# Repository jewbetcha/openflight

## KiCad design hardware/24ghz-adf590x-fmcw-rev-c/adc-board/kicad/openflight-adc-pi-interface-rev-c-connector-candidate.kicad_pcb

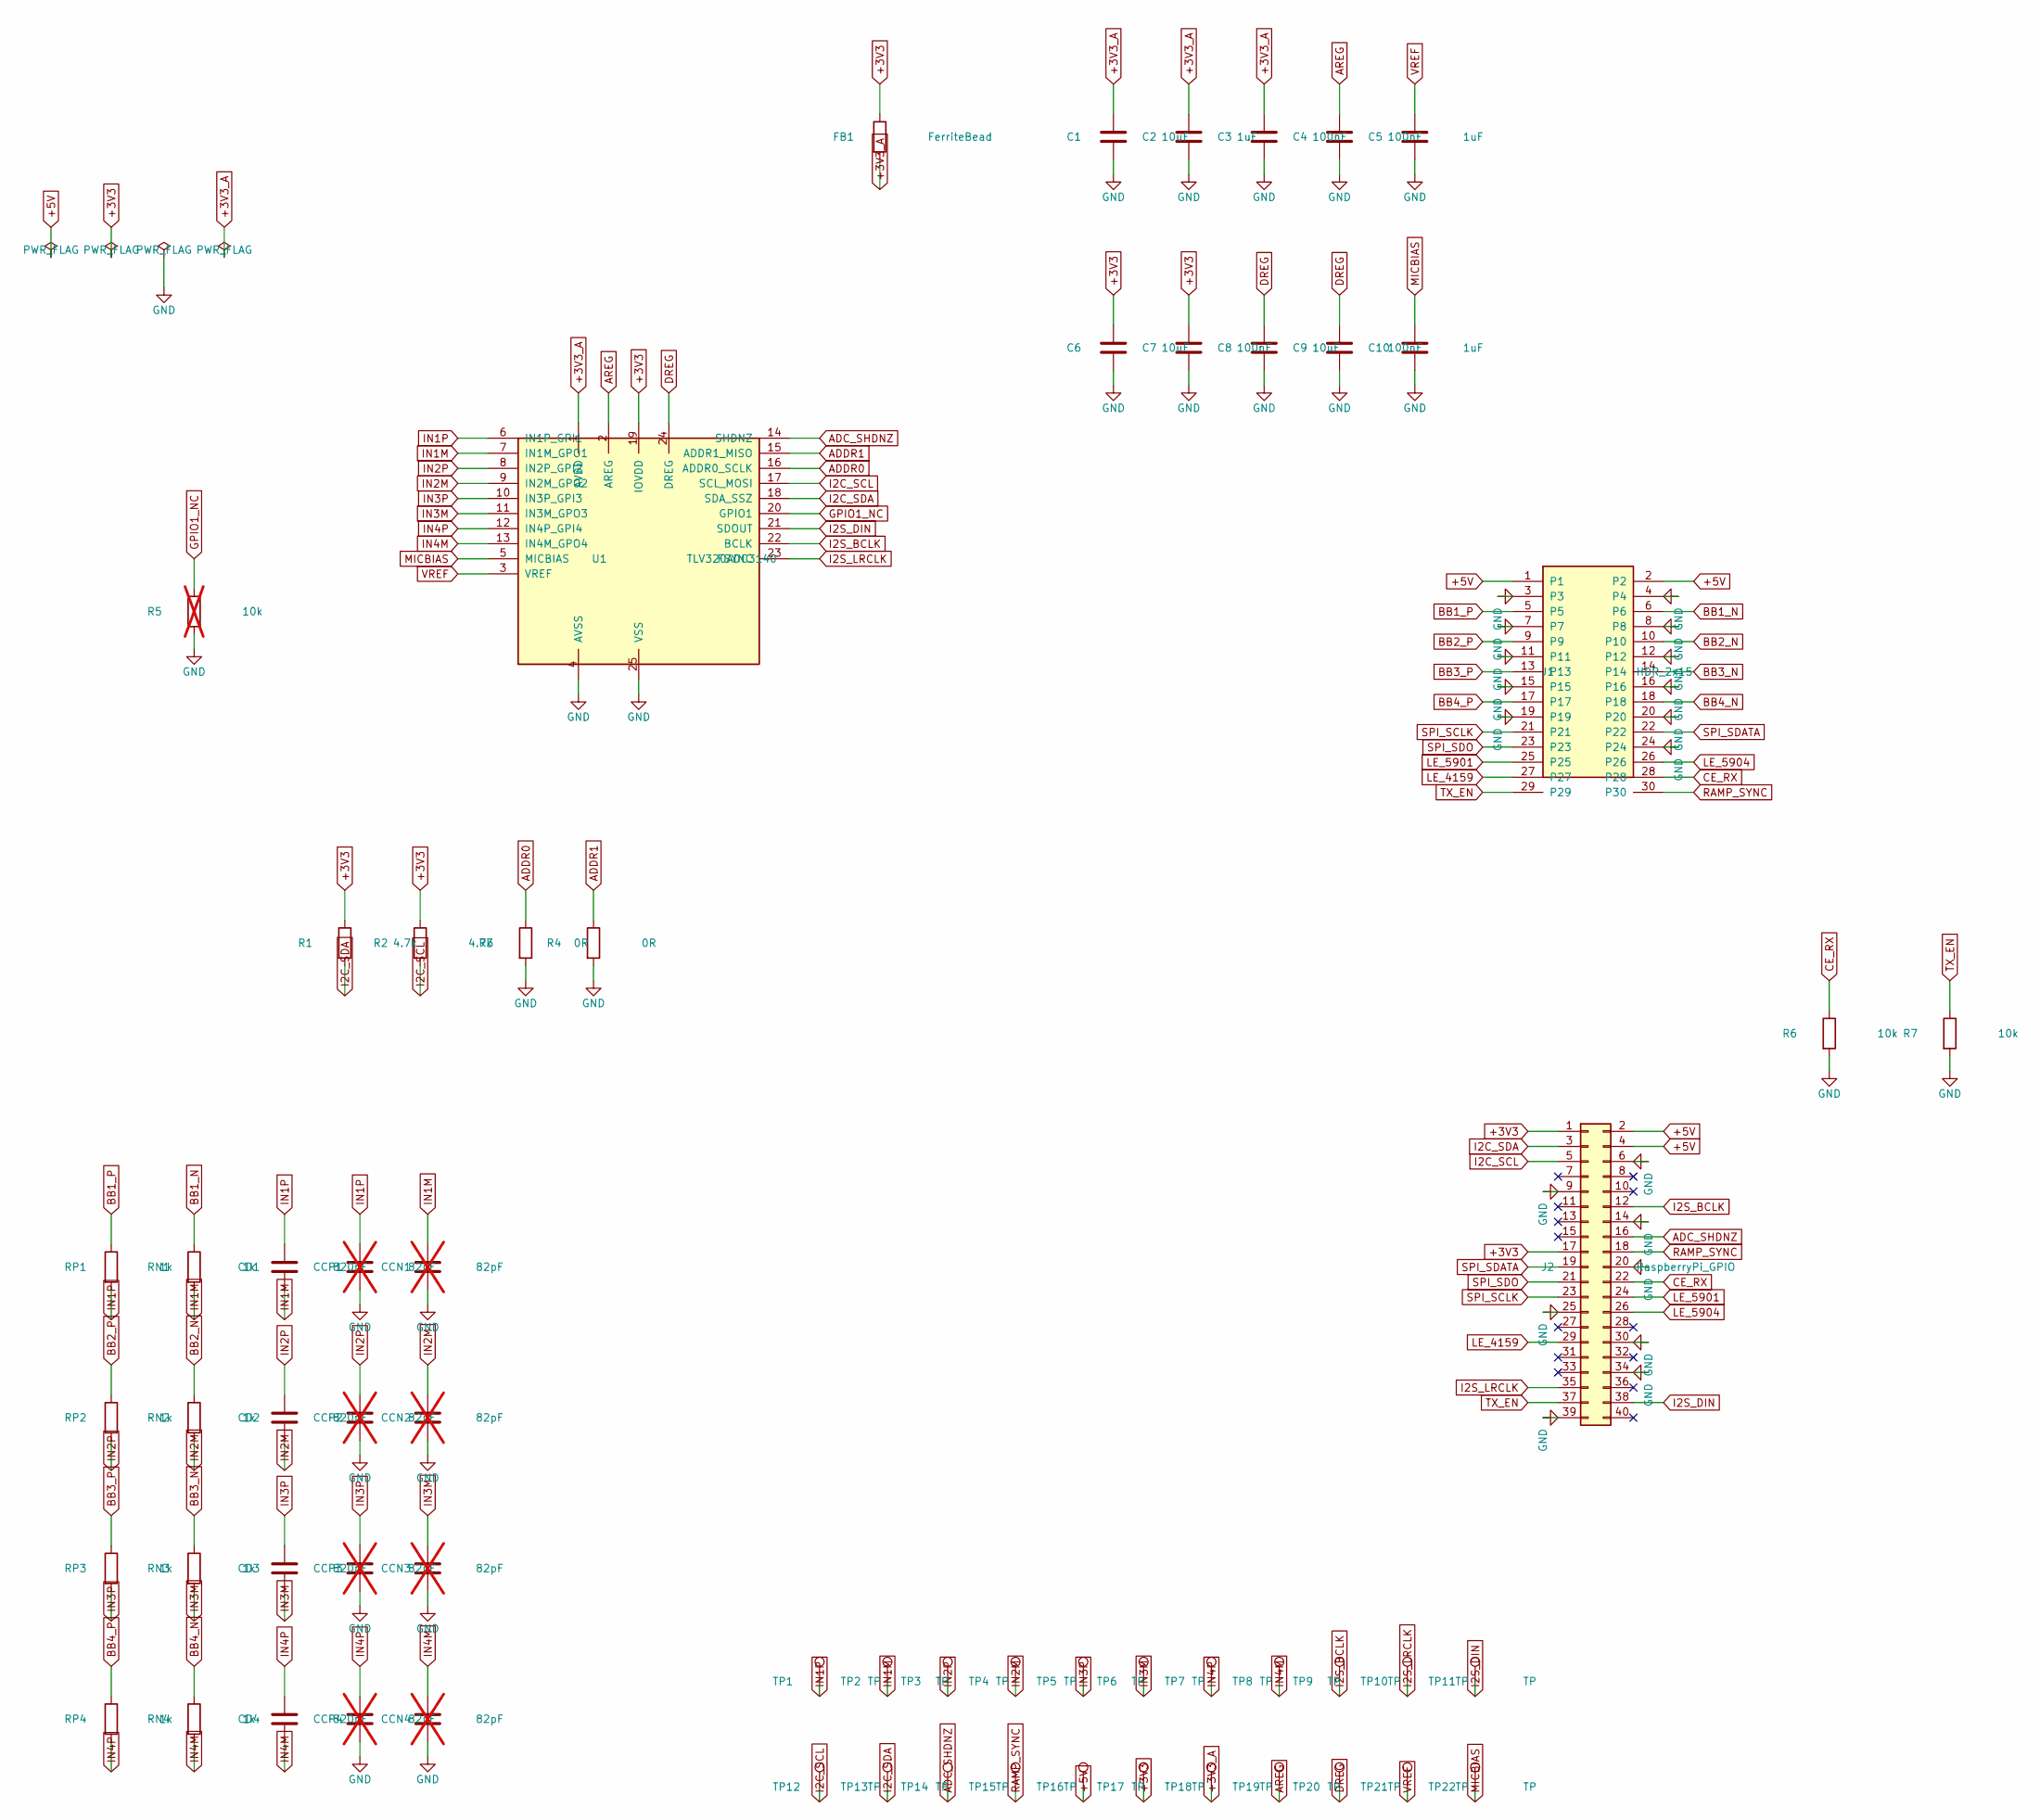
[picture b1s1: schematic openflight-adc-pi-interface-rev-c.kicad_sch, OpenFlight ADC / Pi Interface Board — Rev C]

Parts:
C1, C6, C8: 10uF; C_0402_1005Metric
C2, C5, C10: 1uF; C_0402_1005Metric
C3, C4, C7, C9: 100nF; C_0402_1005Metric
CCN1, CCN2, CCN3, CCN4: 82pF; C_0402_1005Metric; not fitted
CCP1, CCP2, CCP3, CCP4: 82pF; C_0402_1005Metric; not fitted
CD1, CD2, CD3, CD4: 820pF; C_0402_1005Metric
FB1: FerriteBead; R_0402_1005Metric
J1: HDR_2x15; HDR_2x15_1.27MM_SMD; MPN FTSH-115-01-L-DV-K
J2: RaspberryPi_GPIO; PinSocket_2x20_P2.54mm_Vertical; MPN ESQ-120-58-S-D
R1, R2: 4.7k; R_0402_1005Metric
R3, R4: 0R; R_0402_1005Metric
R5: 10k; R_0402_1005Metric; not fitted
R6, R7: 10k; R_0402_1005Metric; MPN RC0402FR-0710KL
RN1, RN2, RN3, RN4: 1k; R_0402_1005Metric
RP1, RP2, RP3, RP4: 1k; R_0402_1005Metric
TP1, TP2, TP3, TP4, TP5, TP6, TP7, TP8, TP9, TP10, TP11, TP12, TP13, TP14, TP15, TP16, TP17, TP18, TP19, TP20, TP21, TP22: TP; TestPoint_Pad_D1.5mm
U1: TLV320ADC3140; TLV320ADC3140_WQFN24; MPN TLV320ADC3140IRTWT

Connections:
+3V3: C6.1, C7.1, FB1.1, J2.1, J2.17, R1.1, R2.1, TP17.1, U1.19 (IOVDD)
+3V3_A: C1.1, C2.1, C3.1, FB1.2, TP18.1, U1.1 (AVDD)
+5V: J1.1, J1.2, J2.2, J2.4, TP16.1
ADC_SHDNZ: J2.16, TP14.1, U1.14 (SHDNZ)
ADDR0: R3.1, U1.16 (ADDR0_SCLK)
ADDR1: R4.1, U1.15 (ADDR1_MISO)
AREG: C4.1, TP19.1, U1.2 (AREG)
BB1_N: J1.6, RN1.1
BB1_P: J1.5, RP1.1
BB2_N: J1.10, RN2.1
BB2_P: J1.9, RP2.1
BB3_N: J1.14, RN3.1
BB3_P: J1.13, RP3.1
BB4_N: J1.18, RN4.1
BB4_P: J1.17, RP4.1
CE_RX: J1.28, J2.22, R6.1
DREG: C8.1, C9.1, TP20.1, U1.24 (DREG)
GND: C1.2, C2.2, C3.2, C4.2, C5.2, C6.2, C7.2, C8.2, C9.2, C10.2, CCN1.2, CCN2.2, CCN3.2, CCN4.2, CCP1.2, CCP2.2, CCP3.2, CCP4.2, J1.3, J1.4, J1.7, J1.8, J1.11, J1.12, J1.15, J1.16, J1.19, J1.20, J1.24, J2.6, J2.9, J2.14, J2.20, J2.25, J2.30, J2.34, J2.39, R3.2, R4.2, R5.2, R6.2, R7.2, U1.4 (AVSS), U1.25 (VSS)
GPIO1_NC: R5.1, U1.20 (GPIO1)
I2C_SCL: J2.5, R2.2, TP12.1, U1.17 (SCL_MOSI)
I2C_SDA: J2.3, R1.2, TP13.1, U1.18 (SDA_SSZ)
I2S_BCLK: J2.12, TP9.1, U1.22 (BCLK)
I2S_DIN: J2.38, TP11.1, U1.21 (SDOUT)
I2S_LRCLK: J2.35, TP10.1, U1.23 (FSYNC)
IN1M: CCN1.1, CD1.2, RN1.2, TP2.1, U1.7 (IN1M_GPO1)
IN1P: CCP1.1, CD1.1, RP1.2, TP1.1, U1.6 (IN1P_GPI1)
IN2M: CCN2.1, CD2.2, RN2.2, TP4.1, U1.9 (IN2M_GPO2)
IN2P: CCP2.1, CD2.1, RP2.2, TP3.1, U1.8 (IN2P_GPI2)
IN3M: CCN3.1, CD3.2, RN3.2, TP6.1, U1.11 (IN3M_GPO3)
IN3P: CCP3.1, CD3.1, RP3.2, TP5.1, U1.10 (IN3P_GPI3)
IN4M: CCN4.1, CD4.2, RN4.2, TP8.1, U1.13 (IN4M_GPO4)
IN4P: CCP4.1, CD4.1, RP4.2, TP7.1, U1.12 (IN4P_GPI4)
LE_4159: J1.27, J2.29
LE_5901: J1.25, J2.24
LE_5904: J1.26, J2.26
MICBIAS: C10.1, TP22.1, U1.5 (MICBIAS)
RAMP_SYNC: J1.30, J2.18, TP15.1
SPI_SCLK: J1.21, J2.23
SPI_SDATA: J1.22, J2.19
SPI_SDO: J1.23, J2.21
TX_EN: J1.29, J2.37, R7.1
VREF: C5.1, TP21.1, U1.3 (VREF)

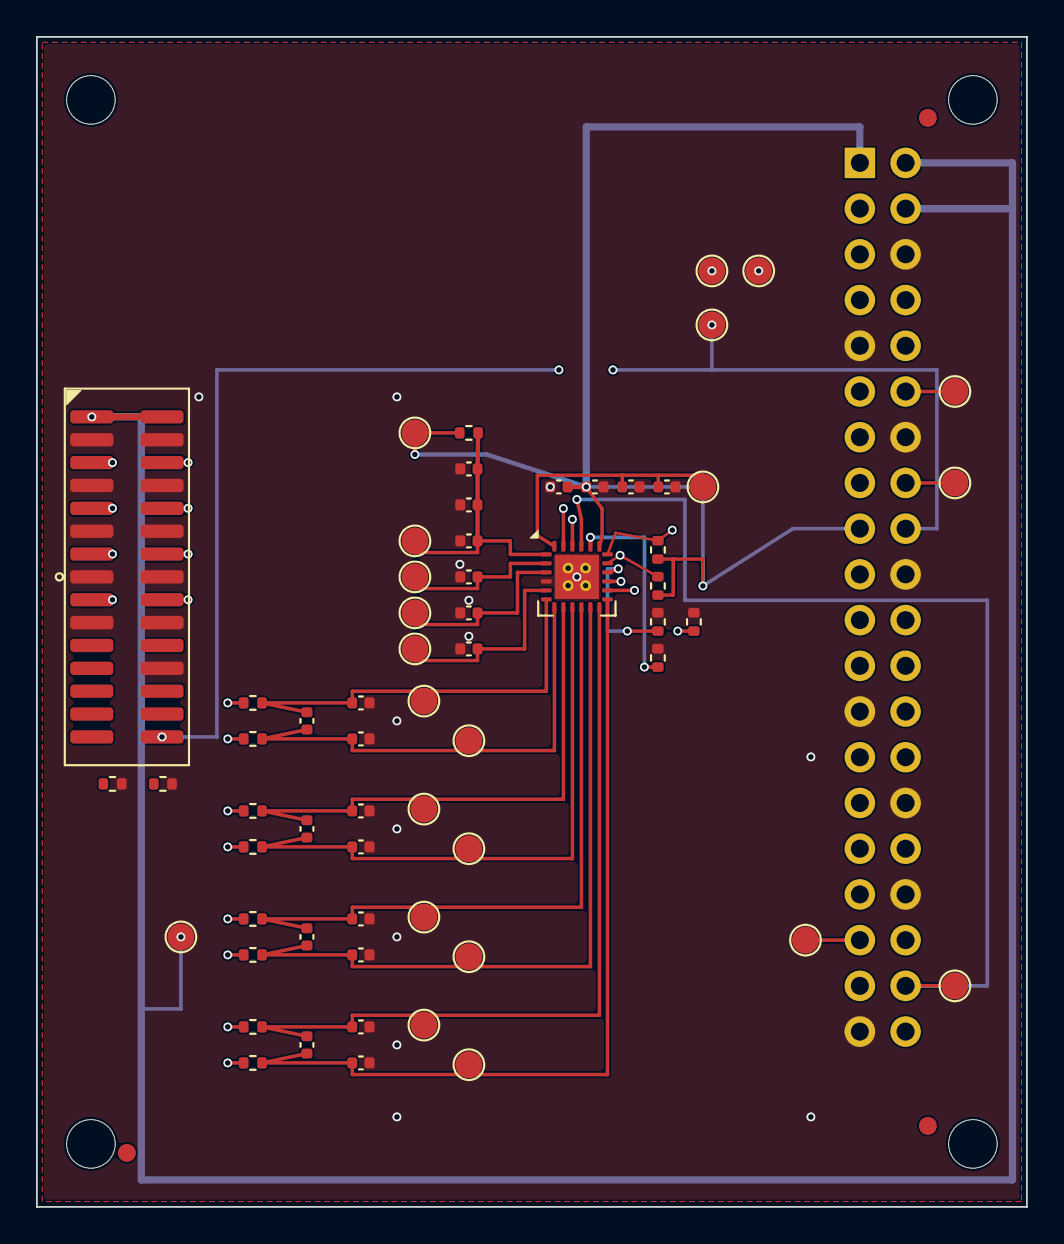
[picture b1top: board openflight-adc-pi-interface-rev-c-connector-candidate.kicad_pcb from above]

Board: 4 copper layers, 55.0 x 65.0 mm, 70 parts (1 on the bottom side), 42 nets.

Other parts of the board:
FID1, FID2, FID3: Fiducial_1mm
H1, H2, H3, H4: MountingHole_2.7mm

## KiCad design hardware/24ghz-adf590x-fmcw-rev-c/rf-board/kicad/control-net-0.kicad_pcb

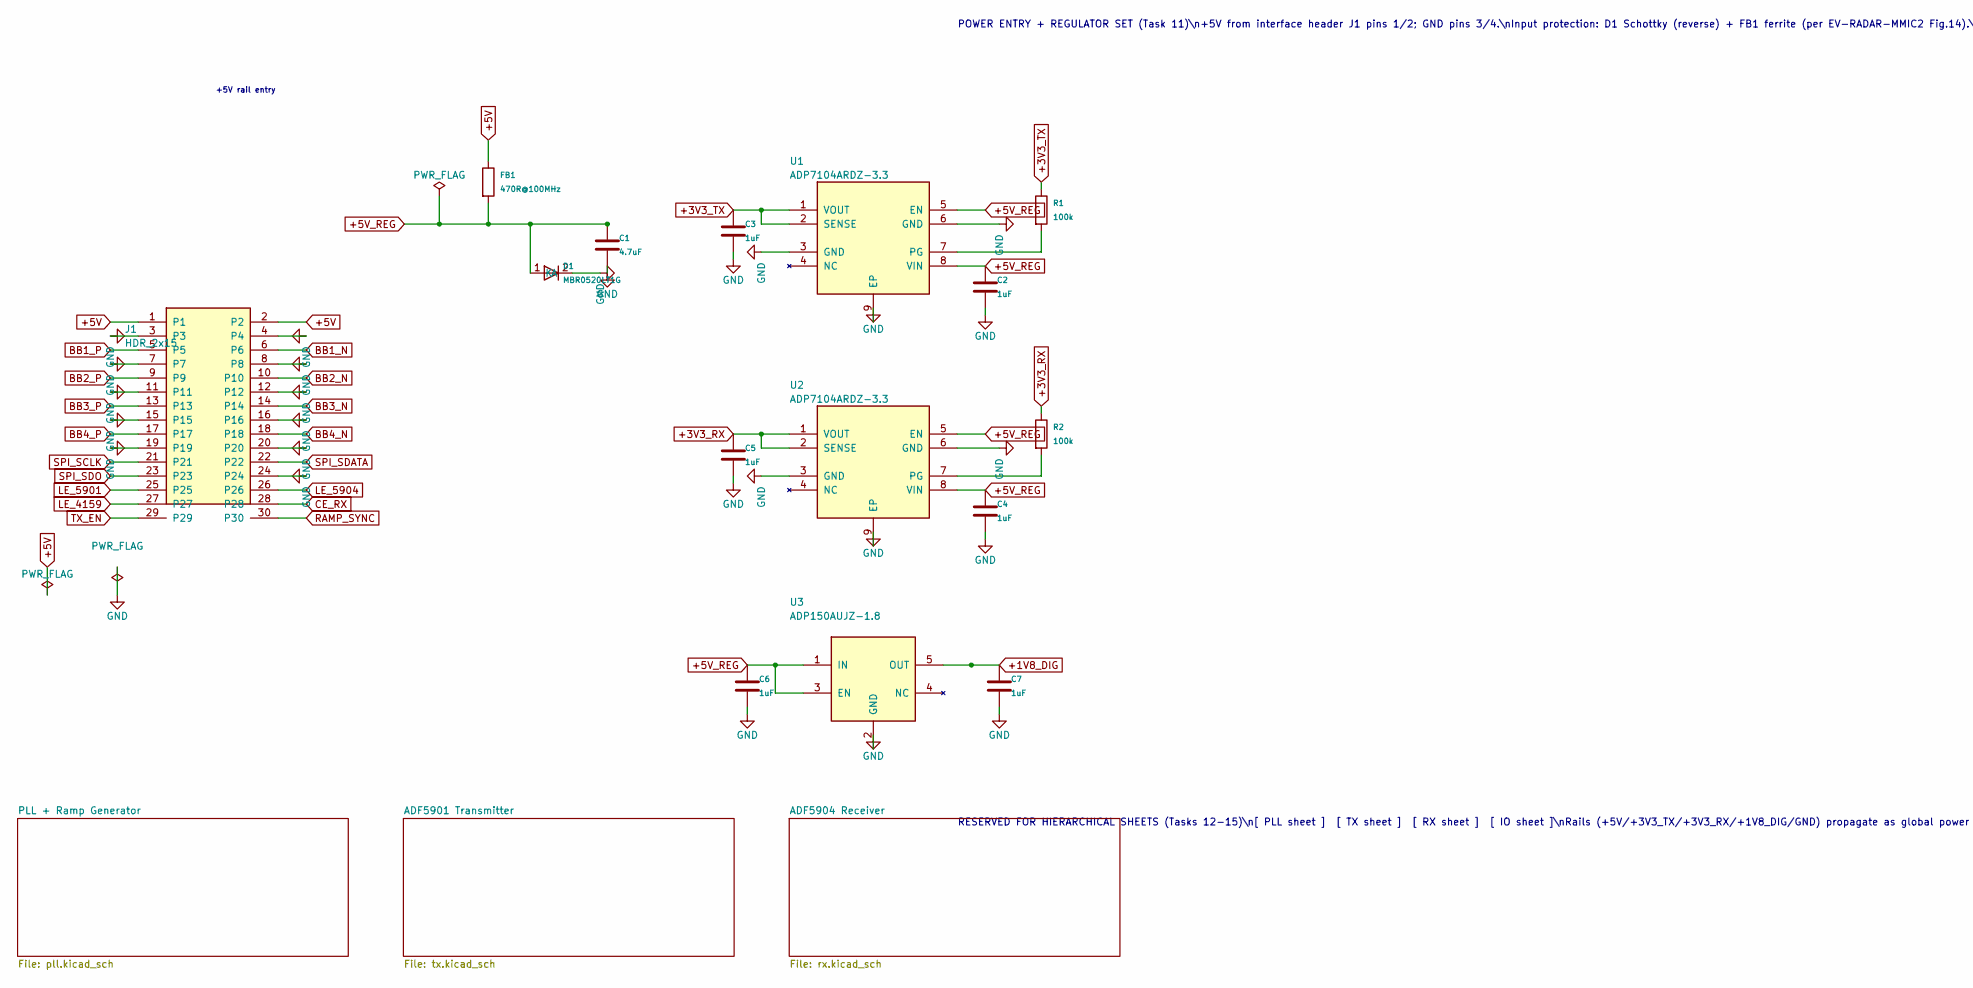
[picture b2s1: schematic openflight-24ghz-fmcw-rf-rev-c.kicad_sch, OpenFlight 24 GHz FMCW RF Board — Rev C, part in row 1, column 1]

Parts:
C1: 4.7uF; C_0603_1608Metric
C2, C3, C4, C5, C6, C7: 1uF; C_0603_1608Metric
D1: MBR0520LT1G; D_SOD-123; MPN MBR0520LT1G
FB1: 470R@100MHz; L_0603_1608Metric; MPN 742792642
J1: HDR_2x15; HDR_2x15_1.27MM_SMD; MPN FTSH-115-01-L-DV-K
R1, R2: 100k; R_0402_1005Metric
U1, U2: ADP7104ARDZ-3.3; ADP7104_SOIC8_EP; MPN ADP7104ARDZ-3.3
U3: ADP150AUJZ-1.8; ADP150_TSOT23_5; MPN ADP150AUJZ-1.8

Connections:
+1V8_DIG: C7.1, U3.5 (OUT); also elsewhere on the board
+3V3_RX: C5.1, R2.1, U2.1 (VOUT), U2.2 (SENSE); also elsewhere on the board
+3V3_TX: C3.1, R1.1, U1.1 (VOUT), U1.2 (SENSE); also elsewhere on the board
+5V: FB1.1, J1.1, J1.2; also elsewhere on the board
+5V_REG: C1.1, C2.1, C4.1, C6.1, D1.1 (K), FB1.2, U1.5 (EN), U1.8 (VIN), U2.5 (EN), U2.8 (VIN), U3.1 (IN), U3.3 (EN)
CE_RX: J1.28; also elsewhere on the board
LE_4159: J1.27; also elsewhere on the board
LE_5901: J1.25; also elsewhere on the board
LE_5904: J1.26; also elsewhere on the board
unnamed: R1.2, U1.7 (PG)
unnamed: R2.2, U2.7 (PG)
RAMP_SYNC: J1.30; also elsewhere on the board
SPI_SCLK: J1.21; also elsewhere on the board
SPI_SDATA: J1.22; also elsewhere on the board
SPI_SDO: J1.23; also elsewhere on the board
TX_EN: J1.29; also elsewhere on the board

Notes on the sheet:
POWER ENTRY + REGULATOR SET (Task 11)\n+5V from interface header J1 pins 1/2; GND pins 3/4.\nInput protection: D1 Schottky (reverse) + FB1 ferrite (per EV-RADAR-MMIC2 Fig.14).\nU1 ADP7104-3.3 -> +3V3_TX (ADF5901). U2 ADP7104-3.3 -> +3V3_RX (ADF5904 + ADF4159 analog).\nU3 ADP150-1.8 -> +1V8_DIG (ADF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
RESERVED FOR HIERARCHICAL SHEETS (Tasks 12-15)\n[ PLL sheet ] [ TX sheet ] [ RX sheet ] [ IO sheet ]\nRails (+5V/+3V3_TX/+3V3_RX/+1V8_DIG/GND) propagate as global power symbols;\nsignals cross via hierarchical pins added by those tasks.
+5V rail entry

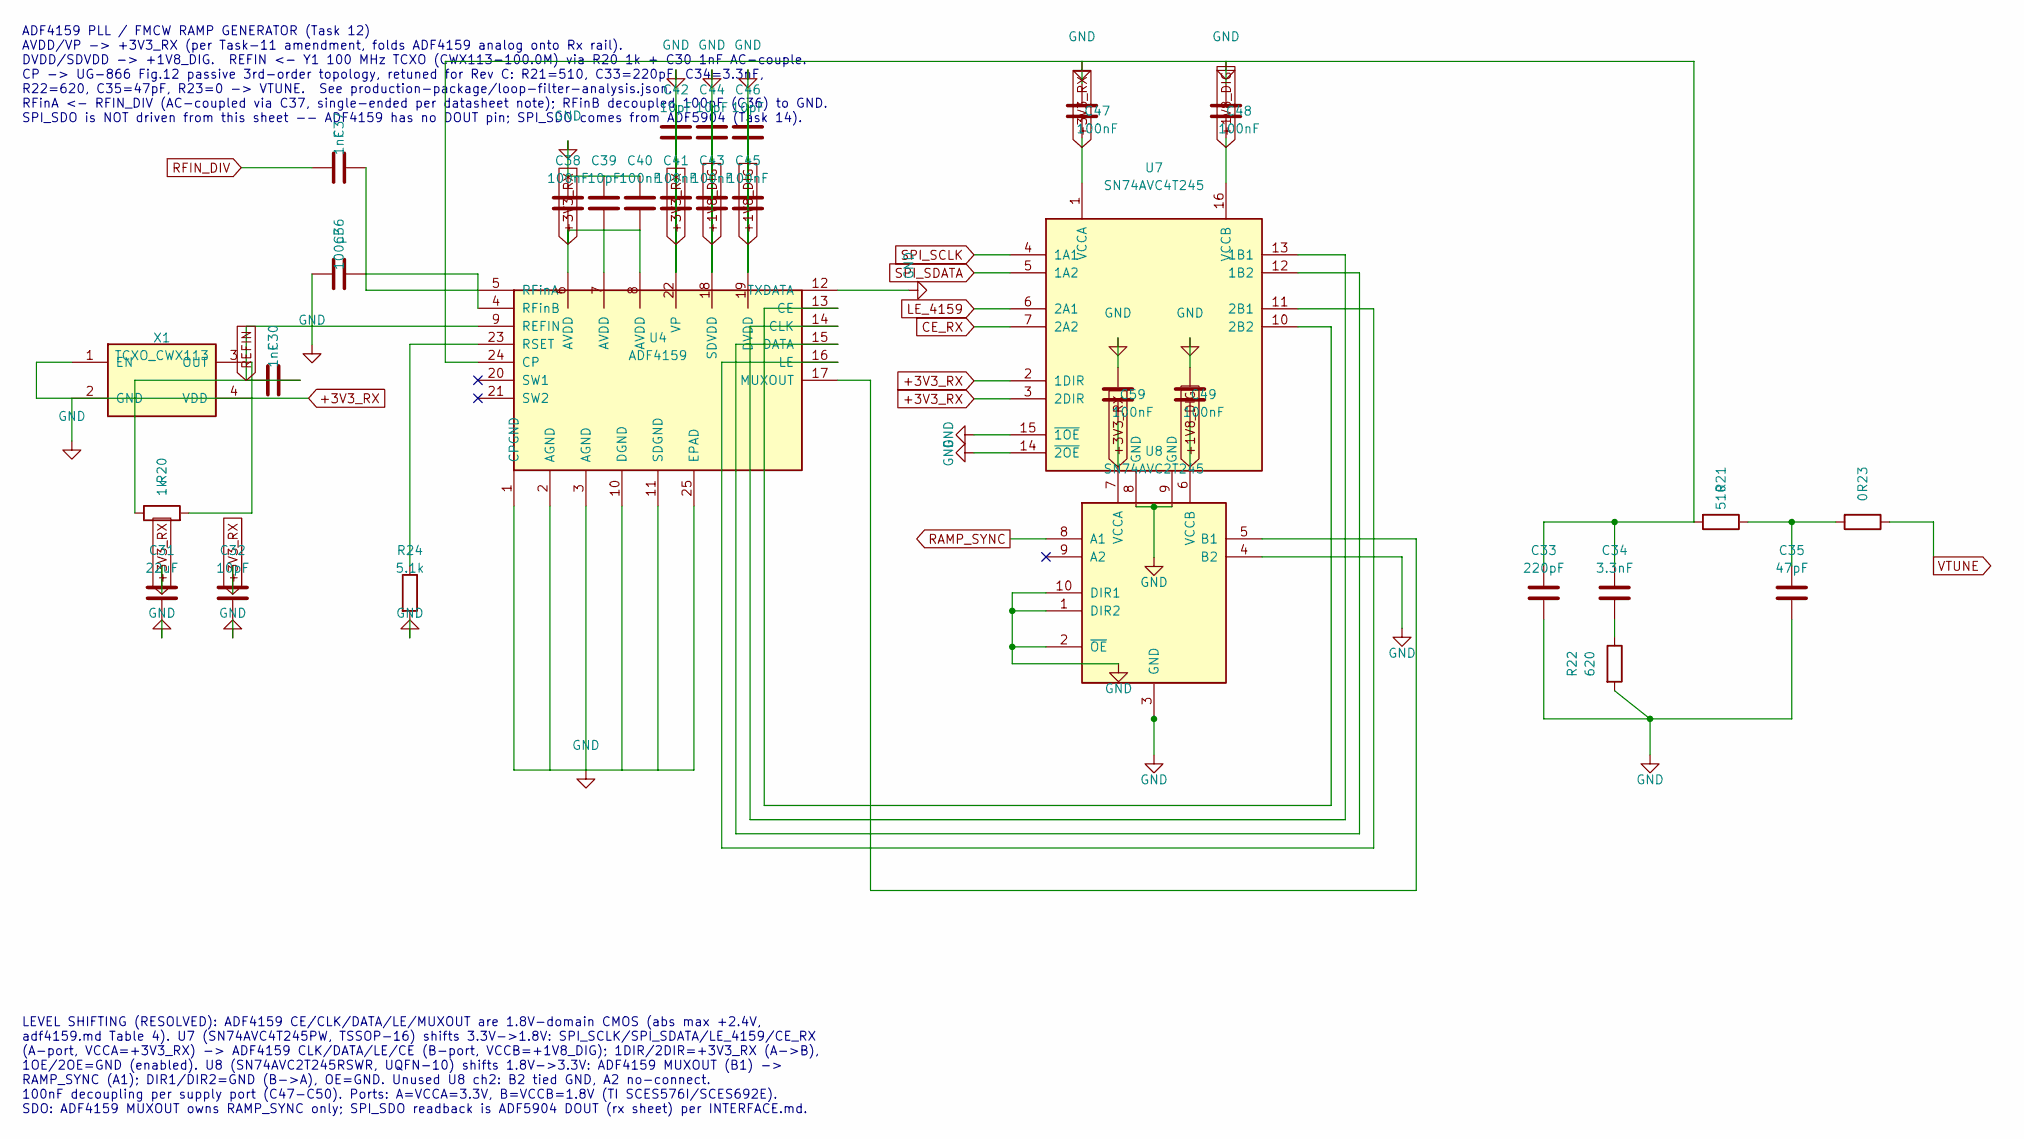
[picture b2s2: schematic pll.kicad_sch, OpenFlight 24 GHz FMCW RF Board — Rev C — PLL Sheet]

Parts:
C30, C37: 1nF; C_0402_1005Metric
C31: 22uF; C_0805_2012Metric
C32, C39, C42, C44, C46: 10pF; C_0402_1005Metric
C33: 220pF; C_0402_1005Metric
C34: 3.3nF; C_0402_1005Metric
C35: 47pF; C_0402_1005Metric
C36: 100pF; C_0402_1005Metric
C38, C40, C41, C43, C45, C47, C48, C49, C59: 100nF; C_0402_1005Metric
R20: 1k; R_0402_1005Metric
R21: 510; R_0402_1005Metric
R22: 620; R_0402_1005Metric
R23: 0; R_0402_1005Metric
R24: 5.1k; R_0402_1005Metric
U4: ADF4159; ADF4159_LFCSP24; MPN ADF4159CCPZ
U7: SN74AVC4T245; TSSOP-16_4.4x5mm_P0.65mm; MPN SN74AVC4T245PW
U8: SN74AVC2T245; Texas_RSW0010A_UQFN-10_1.4x1.8mm_P0.4mm; MPN SN74AVC2T245RSWR
X1: TCXO_CWX113; TCXO_CWX113_SMD4; MPN CWX113-100.0M

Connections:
+1V8_DIG: C43.2, C44.2, C45.2, C46.2, C48.2, C49.2, U4.18 (SDVDD), U4.19 (DVDD), U7.16 (VCCB), U8.6 (VCCB); also elsewhere on the board
+3V3_RX: C31.1, C32.1, C38.2, C39.2, C40.2, C41.2, C42.2, C47.2, C59.2, U4.6 (AVDD), U4.7 (AVDD), U4.8 (AVDD), U4.22 (VP), U7.1 (VCCA), U7.2 (1DIR), U7.3 (2DIR), U8.7 (VCCA), X1.1 (EN), X1.4 (VDD); also elsewhere on the board
CE_RX: U7.7 (2A2); also elsewhere on the board
LE_4159: U7.6 (2A1); also elsewhere on the board
unnamed: C30.2, R20.1
unnamed: U4.13 (CE), U7.10 (2B2)
unnamed: U4.14 (CLK), U7.13 (1B1)
unnamed: U4.15 (DATA), U7.12 (1B2)
unnamed: U4.16 (LE), U7.11 (2B1)
unnamed: U4.17 (MUXOUT), U8.5 (B1)
unnamed: C37.2, U4.5 (RFinA)
unnamed: C36.2, U4.4 (RFinB)
unnamed: R24.1, U4.23 (RSET)
unnamed: R20.2, X1.3 (OUT)
RAMP_SYNC: U8.8 (A1); also elsewhere on the board
REFIN: C30.1, U4.9 (REFIN); also elsewhere on the board
RFIN_DIV: C37.1; also elsewhere on the board
SPI_SCLK: U7.4 (1A1); also elsewhere on the board
SPI_SDATA: U7.5 (1A2); also elsewhere on the board

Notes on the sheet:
ADF4159 PLL / FMCW RAMP GENERATOR (Task 12) AVDD/VP -> +3V3_RX (per Task-11 amendment, folds ADF4159 analog onto Rx rail). DVDD/SDVDD -> +1V8_DIG. REFIN <- Y1 100 MHz TCXO (CWX113-100.0M) via R20 1k + C30 1nF AC-couple. CP -> UG-866 Fig.12 passive 3rd-order topology, retuned for Rev C: R21=510, C33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
LEVEL SHIFTING (RESOLVED): ADF4159 CE/CLK/DATA/LE/MUXOUT are 1.8V-domain CMOS (abs max +2.4V, adf4159.md Table 4). U7 (SN74AVC4T245PW, TSSOP-16) shifts 3.3V->1.8V: SPI_SCLK/SPI_SDATA/LE_4159/CE_RX (A-port, VCCA=+3V3_RX) -> ADF4159 CLK/DATA/LE/CE (B-port, VCCB=+1V8_DIG); 1DIR/2DIR=+3V3_RX (A->B), 1O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

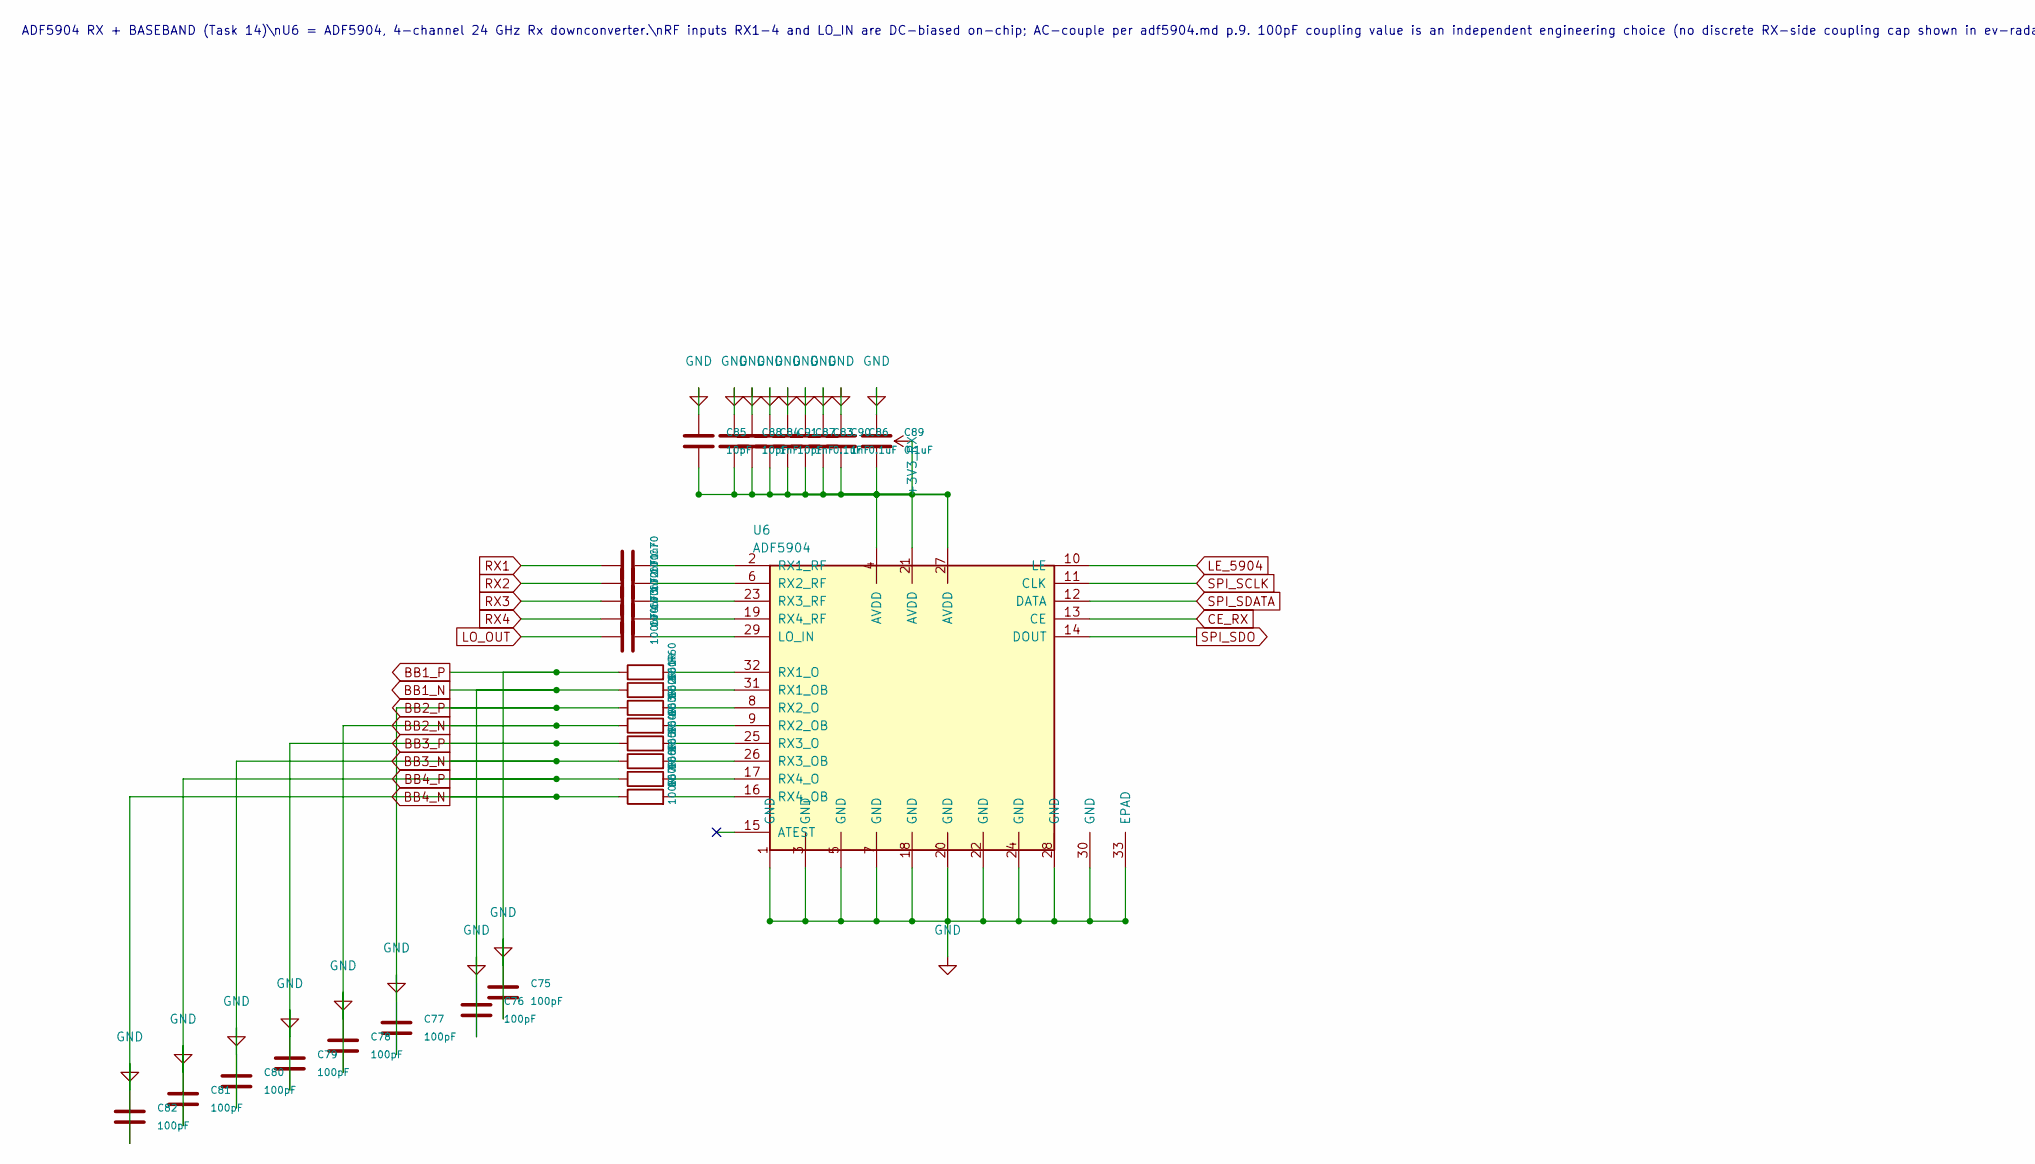
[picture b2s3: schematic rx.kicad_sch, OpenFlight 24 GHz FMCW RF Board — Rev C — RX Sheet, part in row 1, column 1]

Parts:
C70, C71, C72, C73, C74: 100nF; C_0402_1005Metric; MPN 550L104KTT
C75, C76, C77, C78, C79, C80, C81, C82: 100pF; C_0402_1005Metric
C83, C86, C89: 0.1uF; C_0402_1005Metric
C84, C87, C90: 1nF; C_0402_1005Metric
C85, C88, C91: 10pF; C_0402_1005Metric
R60, R61, R62, R63, R64, R65, R66, R67: 100R; R_0402_1005Metric
U6: ADF5904; ADF5904_LFCSP32; MPN ADF5904WCCPZ

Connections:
+3V3_RX: C83.2, C84.2, C85.2, C86.2, C87.2, C88.2, C89.2, C90.2, C91.2, U6.4 (AVDD), U6.21 (AVDD), U6.27 (AVDD); also elsewhere on the board
CE_RX: U6.13 (CE); also elsewhere on the board
LE_5904: U6.10 (LE); also elsewhere on the board
LO_OUT: C74.1; also elsewhere on the board
unnamed: C74.2, U6.29 (LO_IN)
unnamed: R60.2, U6.32 (RX1_O)
unnamed: R61.2, U6.31 (RX1_OB)
unnamed: C70.2, U6.2 (RX1_RF)
unnamed: R62.2, U6.8 (RX2_O)
unnamed: R63.2, U6.9 (RX2_OB)
unnamed: C71.2, U6.6 (RX2_RF)
unnamed: R64.2, U6.25 (RX3_O)
unnamed: R65.2, U6.26 (RX3_OB)
unnamed: C72.2, U6.23 (RX3_RF)
unnamed: R66.2, U6.17 (RX4_O)
unnamed: R67.2, U6.16 (RX4_OB)
unnamed: C73.2, U6.19 (RX4_RF)
RX1: C70.1; also elsewhere on the board
RX2: C71.1; also elsewhere on the board
RX3: C72.1; also elsewhere on the board
RX4: C73.1; also elsewhere on the board
SPI_SCLK: U6.11 (CLK); also elsewhere on the board
SPI_SDATA: U6.12 (DATA); also elsewhere on the board
SPI_SDO: U6.14 (DOUT); also elsewhere on the board

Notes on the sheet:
ADF5904 RX + BASEBAND (Task 14)\nU6 = ADF5904, 4-channel 24 GHz Rx downconverter.\nRF inputs RX1-4 and LO_IN are DC-biased on-chip; AC-couple per adf5904.md p.9. 100pF coupling value is an independent engineering choice (no discrete RX-side coupling cap shown in ev-radar-mmic2.md; Fig.23 there cove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

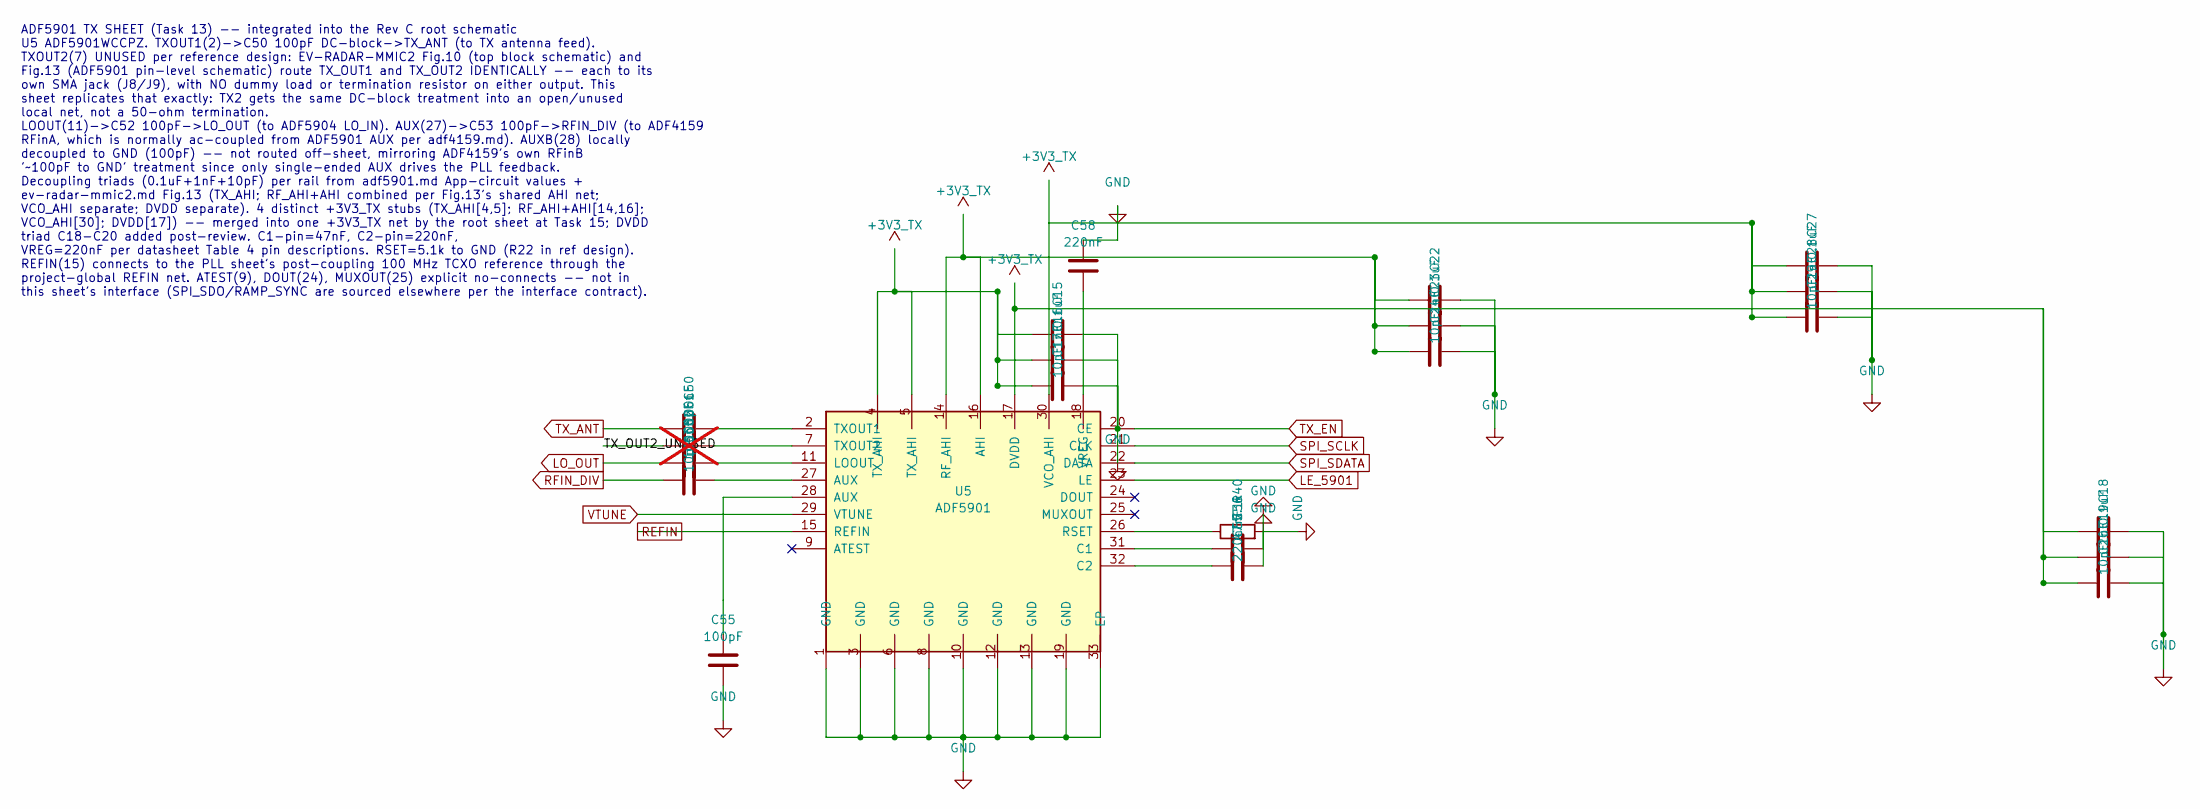
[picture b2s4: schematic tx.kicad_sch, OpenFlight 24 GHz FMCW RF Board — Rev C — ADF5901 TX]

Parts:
C15, C18, C22, C27: 0.1uF; C_0402_1005Metric
C16, C19, C23, C28: 1nF; C_0402_1005Metric
C17, C20, C24, C29: 10pF; C_0402_1005Metric
C50, C52: 100nF; C_0402_1005Metric; MPN 550L104KTT
C51: 100pF; C_0402_1005Metric; not fitted
C53: 10pF; C_0201_0603Metric; MPN 0201ZK100FBSTR
C55: 100pF; C_0402_1005Metric
C56: 47nF; C_0402_1005Metric
C57, C58: 220nF; C_0402_1005Metric
R40: 5.1k; R_0402_1005Metric
U5: ADF5901; ADF5901_LFCSP32; MPN ADF5901WCCPZ

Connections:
+3V3_TX: C15.1, C16.1, C17.1, C18.1, C19.1, C20.1, C22.1, C23.1, C24.1, C27.1, C28.1, C29.1, U5.4 (TX_AHI), U5.5 (TX_AHI), U5.14 (RF_AHI), U5.16 (AHI), U5.17 (DVDD), U5.30 (VCO_AHI); also elsewhere on the board
/ADF5901 Transmitter/TX_OUT2_UNUSED: C51.1
LE_5901: U5.23 (LE); also elsewhere on the board
LO_OUT: C52.1; also elsewhere on the board
unnamed: C53.2, U5.27 (AUX)
unnamed: C55.1, U5.28 (AUX)
unnamed: C56.1, U5.31 (C1)
unnamed: C57.1, U5.32 (C2)
unnamed: C52.2, U5.11 (LOOUT)
unnamed: R40.1, U5.26 (RSET)
unnamed: C50.2, U5.2 (TXOUT1)
unnamed: C51.2, U5.7 (TXOUT2)
unnamed: C58.2, U5.18 (VREG)
REFIN: U5.15 (REFIN); also elsewhere on the board
RFIN_DIV: C53.1; also elsewhere on the board
SPI_SCLK: U5.21 (CLK); also elsewhere on the board
SPI_SDATA: U5.22 (DATA); also elsewhere on the board
TX_ANT: C50.1; also elsewhere on the board
TX_EN: U5.20 (CE); also elsewhere on the board

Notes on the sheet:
ADF5901 TX SHEET (Task 13) -- integrated into the Rev C root schematic U5 ADF5901WCCPZ. TXOUT1(2)->C50 100pF DC-block->TX_ANT (to TX antenna feed). TXOUT2(7) UNUSED per reference design: EV-RADAR-MMIC2 Fig.10 (top block schematic) and Fig.13 (ADF5901 pin-level schematic) route TX_OUT1 and TX_OUT2 I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

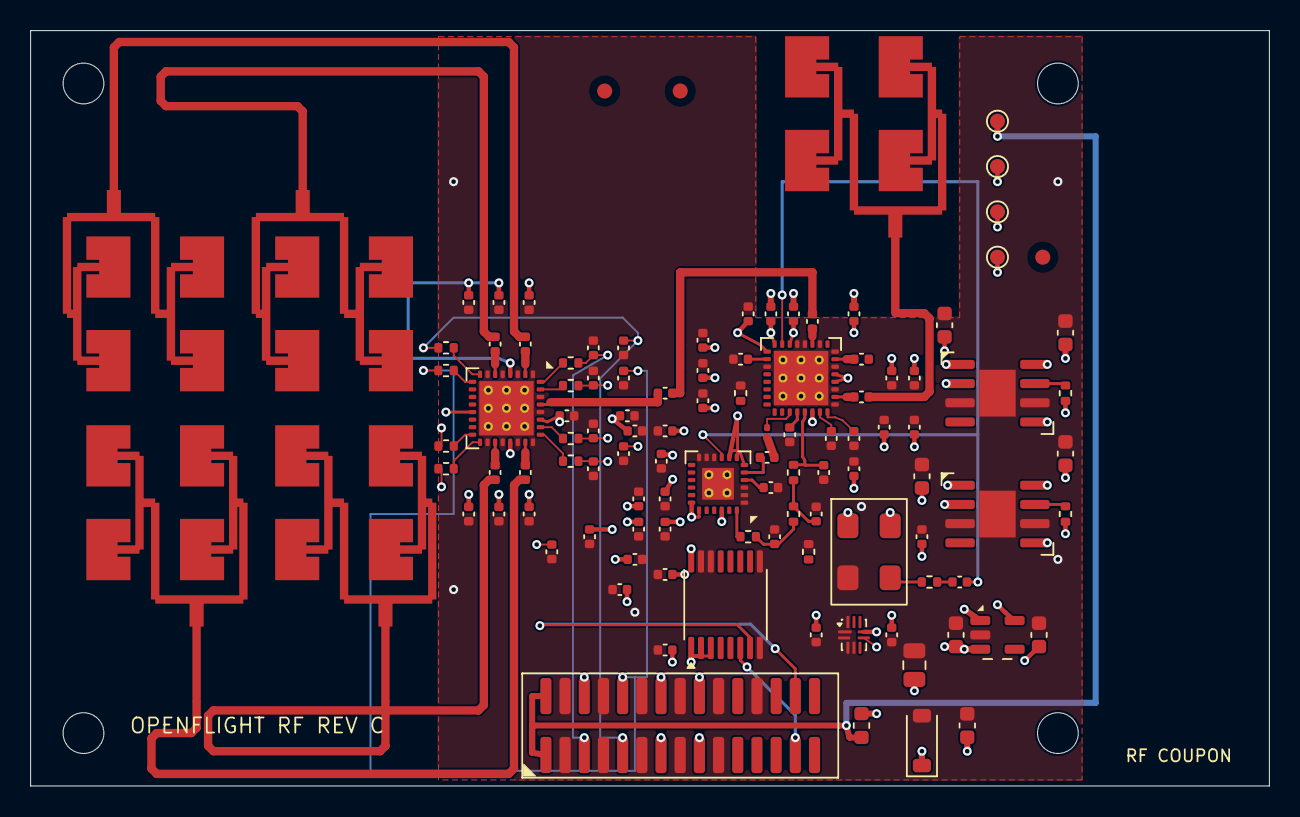
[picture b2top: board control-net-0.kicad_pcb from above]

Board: 4 copper layers, 82.0 x 50.0 mm, 114 parts (0 on the bottom side), 69 nets.

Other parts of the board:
ANT_RX1: RX1; RX_SUBARRAY_2X2
ANT_RX2: RX2; RX_SUBARRAY_2X2
ANT_RX3: RX3; RX_SUBARRAY_2X2
ANT_RX4: RX4; RX_SUBARRAY_2X2
ANT_TX1: TX_ANT; TX_ARRAY_2X2
FID1, FID2, FID3: Fiducial; Fiducial_1mm_Mask2mm
H1, H2, H3, H4: M2.5; MountingHole_2.7mm
TP1: +5V; TestPoint_Pad_D1.0mm
TP2: +3V3_TX; TestPoint_Pad_D1.0mm
TP3: +3V3_RX; TestPoint_Pad_D1.0mm
TP4: +1V8_DIG; TestPoint_Pad_D1.0mm

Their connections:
+1V8_DIG: TP4.1; also elsewhere on the board
+3V3_RX: TP3.1; also elsewhere on the board
+3V3_TX: TP2.1; also elsewhere on the board
+5V: TP1.1; also elsewhere on the board
RX1: ANT_RX1.1; also elsewhere on the board
RX2: ANT_RX2.1; also elsewhere on the board
RX3: ANT_RX3.1; also elsewhere on the board
RX4: ANT_RX4.1; also elsewhere on the board
TX_ANT: ANT_TX1.1; also elsewhere on the board
